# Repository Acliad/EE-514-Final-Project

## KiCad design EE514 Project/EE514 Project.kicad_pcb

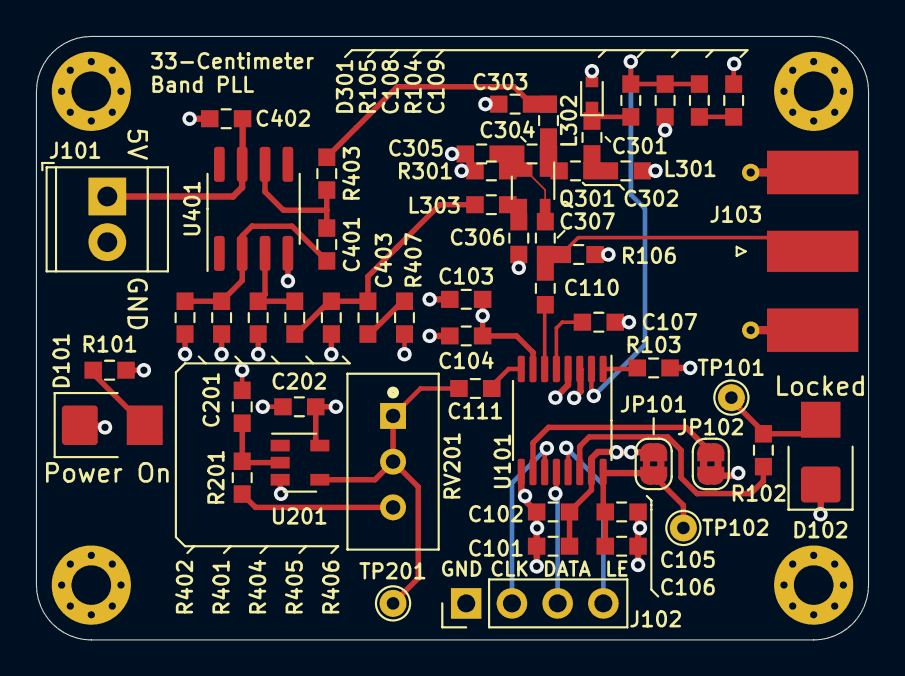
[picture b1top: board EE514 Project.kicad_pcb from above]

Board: 4 copper layers, 46.2 x 33.5 mm, 61 parts (0 on the bottom side), 31 nets.

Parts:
C101, C103, C106: 0.1uF; C_0603_1608Metric_Pad0.98x0.95mm_HandSolder
C102, C104, C105: 10pF; C_0603_1608Metric_Pad0.98x0.95mm_HandSolder
C107, C110, C303, C306: 30pF; C_0603_1608Metric_Pad0.98x0.95mm_HandSolder
C108: 56pF; C_0603_1608Metric_Pad0.98x0.95mm_HandSolder
C109, C111: 1.3nF; C_0603_1608Metric_Pad0.98x0.95mm_HandSolder
C201, C202, C402: 0.1nF; C_0603_1608Metric_Pad0.98x0.95mm_HandSolder
C301, C302, C307: 36pF; C_0603_1608Metric_Pad0.98x0.95mm_HandSolder
C304: 15pF; C_0603_1608Metric_Pad0.98x0.95mm_HandSolder
C305: 5.4pF; C_0603_1608Metric_Pad0.98x0.95mm_HandSolder
C401, C403: 12nF; C_0603_1608Metric_Pad0.98x0.95mm_HandSolder
D101, D102: LED; LED_Kingbright_AA3528V_3.5x2.8mm_handsolder
D301: SMV1276-079LF; D_SOD-523
H101, H102, H103, H104: MountingHole_Pad; MountingHole_2.2mm_M2_Pad_Via
J101: Screw_Terminal_01x02; TerminalBlock_TE_282834-2_1x02_P2.54mm_Horizontal
J102: Conn_01x04; PinHeader_1x04_P2.54mm_Vertical
J103: SMA; SMA_Molex_73251-1153_EdgeMount_Horizontal
JP101, JP102: Jumper_2_Bridged; SolderJumper-2_P1.3mm_Bridged2Bar_RoundedPad1.0x1.5mm
L301: 1.6nH; L_0603_1608Metric_Pad0.98x0.95mm_HandSolder
L302, L303: 39nH; L_0603_1608Metric_Pad0.98x0.95mm_HandSolder
Q301: BFP620; SOT-343_2.0x1.25mm_P1.3mm
R101, R102: 1k; R_0603_1608Metric_Pad0.98x0.95mm_HandSolder
R103: 10k; R_0603_1608Metric_Pad0.98x0.95mm_HandSolder
R104: 46.9k; R_0603_1608Metric_Pad0.98x0.95mm_HandSolder
R105: 220k; R_0603_1608Metric_Pad0.98x0.95mm_HandSolder
R106: 51; R_0603_1608Metric_Pad0.98x0.95mm_HandSolder
R201, R301: 100; R_0603_1608Metric_Pad0.98x0.95mm_HandSolder
R401: 1.3k; R_0603_1608Metric_Pad0.98x0.95mm_HandSolder
R402: 1.5k; R_0603_1608Metric_Pad0.98x0.95mm_HandSolder
R403: 3.3k; R_0603_1608Metric_Pad0.98x0.95mm_HandSolder
R404: 110k; R_0603_1608Metric_Pad0.98x0.95mm_HandSolder
R405: 75k; R_0603_1608Metric_Pad0.98x0.95mm_HandSolder
R406: 124; R_0603_1608Metric_Pad0.98x0.95mm_HandSolder
R407: 18; R_0603_1608Metric_Pad0.98x0.95mm_HandSolder
RV201: 1k; Potentiometer_Bourns_PV36W_Vertical
TP101, TP102, TP201: TestPoint; TestPoint_THTPad_D1.5mm_Drill0.7mm
U101: ADF4117; TSSOP-16_4.4x5mm_P0.65mm
U201: NC7SZ04; SOT-23-5
U401: TLC2201; SOIC-8_3.9x4.9mm_P1.27mm

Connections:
+5V: C101.1, C102.1, C103.1, C104.1, C202.1, C402.1, J101.1, JP101.1, JP102.1, R101.2, R401.1, R406.1, R407.1, U101.7, U101.15, U201.5, U401.7
/CLK_PLL: J102.2, U101.11
/CP_OUT: C108.1, R104.1, R105.2, U101.2
/DATA_PLL: J102.3, U101.12
/LE_PLL: J102.4, U101.13
/LOCKED: R102.2, U101.14
/RF_OUT: C110.1, C307.1, J103.1, R106.1
/Reference Oscillator/10MHz_REF_OUT: C111.2, RV201.1, RV201.2, TP201.1, U201.4
/VCO/Bias Regulator/V_BIAS_COLLECTOR: C403.2, L303.1, R405.1, R406.2
/VCO/V_BIAS_BASE: C303.1, L302.2, R403.1
/V_TUNE: C301.2, D301.1, R105.1
/Vp: C105.1, C106.1, JP102.2, TP102.1, U101.16
GND: C101.2, C102.2, C103.2, C104.2, C105.2, C106.2, C107.2, C108.2, C109.2, C201.2, C202.2, C303.2, C305.2, C306.1, C402.2, D101.1, D102.1, D301.2, H101.1, H102.1, H103.1, H104.1, J101.2, J102.1, J103.2, L301.2, R103.2, R106.2, R301.2, R402.2, R404.2, U101.3, U101.4, U101.9, U201.3, U401.4
unnamed: C107.1, U101.5
unnamed: C109.1, R104.2
unnamed: C110.2, U101.6
unnamed: C111.1, U101.8
unnamed: C201.1, R201.2, U201.2
unnamed: C301.1, C302.2, L301.1
unnamed: C302.1, C304.1, L302.1, Q301.1
unnamed: C304.2, C305.1, C307.2, Q301.2, Q301.4, R301.1
unnamed: C306.2, L303.2, Q301.3
unnamed: C401.1, R403.2, U401.6
unnamed: C401.2, R401.2, R402.1, U401.2
unnamed: C403.1, R407.2
unnamed: D101.2, R101.1
unnamed: D102.2, R102.1, TP101.1
unnamed: JP101.2, U101.10
unnamed: R103.1, U101.1
unnamed: R201.1, RV201.3
unnamed: R404.1, R405.2, U401.3

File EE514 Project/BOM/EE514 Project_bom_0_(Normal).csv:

References,Value,Digi-Key PN,Quantity Per PCB,Footprint,Datasheet
C305,5.4pF,399-16205-1-ND,1,C_0603_1608Metric_Pad0.98x0.95mm_HandSolder,~
"C102, C104, C105",10pF,399-C0603C100J3HAC7867CT-ND,3,C_0603_1608Metric_Pad0.98x0.95mm_HandSolder,~
C304,15pF,311-3878-1-ND,1,C_0603_1608Metric_Pad0.98x0.95mm_HandSolder,~
"C107, C110, C303, C306",30pF,311-3352-1-ND,4,C_0603_1608Metric_Pad0.98x0.95mm_HandSolder,~
"C301, C302, C307",36pF,CC0603GRNPO9BN360,3,C_0603_1608Metric_Pad0.98x0.95mm_HandSolder,~
C108,56pF,399-C0603C560J5GAC7867CT-ND,1,C_0603_1608Metric_Pad0.98x0.95mm_HandSolder,~
"C201, C202, C402",0.1nF,399-C0603C101G1HAC7867CT-ND,3,C_0603_1608Metric_Pad0.98x0.95mm_HandSolder,~
C109,1.3nF,399-15364-1-ND,1,C_0603_1608Metric_Pad0.98x0.95mm_HandSolder,~
"C401, C403",12nF,399-C0603C123K5RAC7867CT-ND,2,C_0603_1608Metric_Pad0.98x0.95mm_HandSolder,~
"C101, C103, C106",0.1uF,399-C0603C104Z3VAC7867CT-ND,3,C_0603_1608Metric_Pad0.98x0.95mm_HandSolder,~
D101,LED,754-1534-1-ND,1,LED_Kingbright_AA3528V_3.5x2.8mm_handsolder,~
D102,LED,754-1528-1-ND,1,LED_Kingbright_AA3528V_3.5x2.8mm_handsolder,~
D301,SMV1276-079LF,863-1730-1-ND,1,D_SOD-523,~
J102,Conn_01x04,732-5316-ND,1,PinHeader_1x04_P2.54mm_Vertical,~
J103,SMA,WM17359-ND,1,SMA_Molex_73251-1153_EdgeMount_Horizontal, ~
J101,Screw_Terminal_01x02,A98333-ND,1,TerminalBlock_TE_282834-2_1x02_P2.54mm_Horizontal,~
L301,1.6nH,490-15806-1-ND,1,L_0603_1608Metric_Pad0.98x0.95mm_HandSolder,~
"L302, L303",39nH,732-7447860139GCT-ND,2,L_0603_1608Metric_Pad0.98x0.95mm_HandSolder,~
Q301,BFP620,BFP620H7764XTSA1CT-ND,1,SOT-343_2.0x1.25mm_P1.3mm,~
R407,18,311-18.0HRCT-ND,1,R_0603_1608Metric_Pad0.98x0.95mm_HandSolder,~
R106,51,311-51.0HRCT-ND,0,R_0603_1608Metric_Pad0.98x0.95mm_HandSolder,~
"R201, R301",100,311-100HRCT-ND,2,R_0603_1608Metric_Pad0.98x0.95mm_HandSolder,~
R406,124,311-124HRCT-ND,1,R_0603_1608Metric_Pad0.98x0.95mm_HandSolder,~
"R101, R102",1k,311-1.00KHRCT-ND,2,R_0603_1608Metric_Pad0.98x0.95mm_HandSolder,~
R401,1.3k,311-1.30KHRCT-ND,1,R_0603_1608Metric_Pad0.98x0.95mm_HandSolder,~
R402,1.5k,311-1.50KHRCT-ND,1,R_0603_1608Metric_Pad0.98x0.95mm_HandSolder,~
R403,3.3k,311-3.30KHRCT-ND,1,R_0603_1608Metric_Pad0.98x0.95mm_HandSolder,~
R103,10k,311-10.0KHRCT-ND,0,R_0603_1608Metric_Pad0.98x0.95mm_HandSolder,~
R104,46.9k,311-47.0KHRCT-ND,1,R_0603_1608Metric_Pad0.98x0.95mm_HandSolder,~
R405,75k,311-75.0KHRCT-ND,1,R_0603_1608Metric_Pad0.98x0.95mm_HandSolder,~
R404,110k,13-AC0603FR-07110KLCT-ND,1,R_0603_1608Metric_Pad0.98x0.95mm_HandSolder,~
R105,220k,311-220KHRCT-ND,1,R_0603_1608Metric_Pad0.98x0.95mm_HandSolder,~
RV201,1k,490-2874-ND,1,Potentiometer_Bourns_PV36W_Vertical,~
U101,ADF4117,ADF4117BRUZ-RL7CT-ND,1,TSSOP-16_4.4x5mm_P0.65mm,https://www.analog.com/media/en/technical-documentation/data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
U201,NC7SZ04,NC7SZ04M5XCT-ND,1,SOT-23-5,https://rocelec.widen.net/view/pdf/vg5irfcitj/ONSM-S-A000359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
U401,TLC2201,296-7061-1-ND,1,SOIC-8_3.9x4.9mm_P1.27mm,https://www.ti.com/lit/ds/symlink/tlc2201.pdf?ts=16372675255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





Component Groups:,36
Component Count:,51
Fitted Components:,49
Number of PCBs:,1
Total components:,49
Schematic Version:,0
Schematic Date:,
PCB Variant:,normal
BoM Date:,"Friday, November 26, 2021 at 11:04:15 PM"
Schematic Source:,EE514 Project.sch
KiCad Version:,Eeschema (5.1.6-0-10_14)

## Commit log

2021-11-26 Started schematic
2021-11-26 Updated pot value
2021-11-27 Finished layout and generated gerbers
2021-11-27 Added BOM
2021-11-28 Added DC blocking cap to ref in
